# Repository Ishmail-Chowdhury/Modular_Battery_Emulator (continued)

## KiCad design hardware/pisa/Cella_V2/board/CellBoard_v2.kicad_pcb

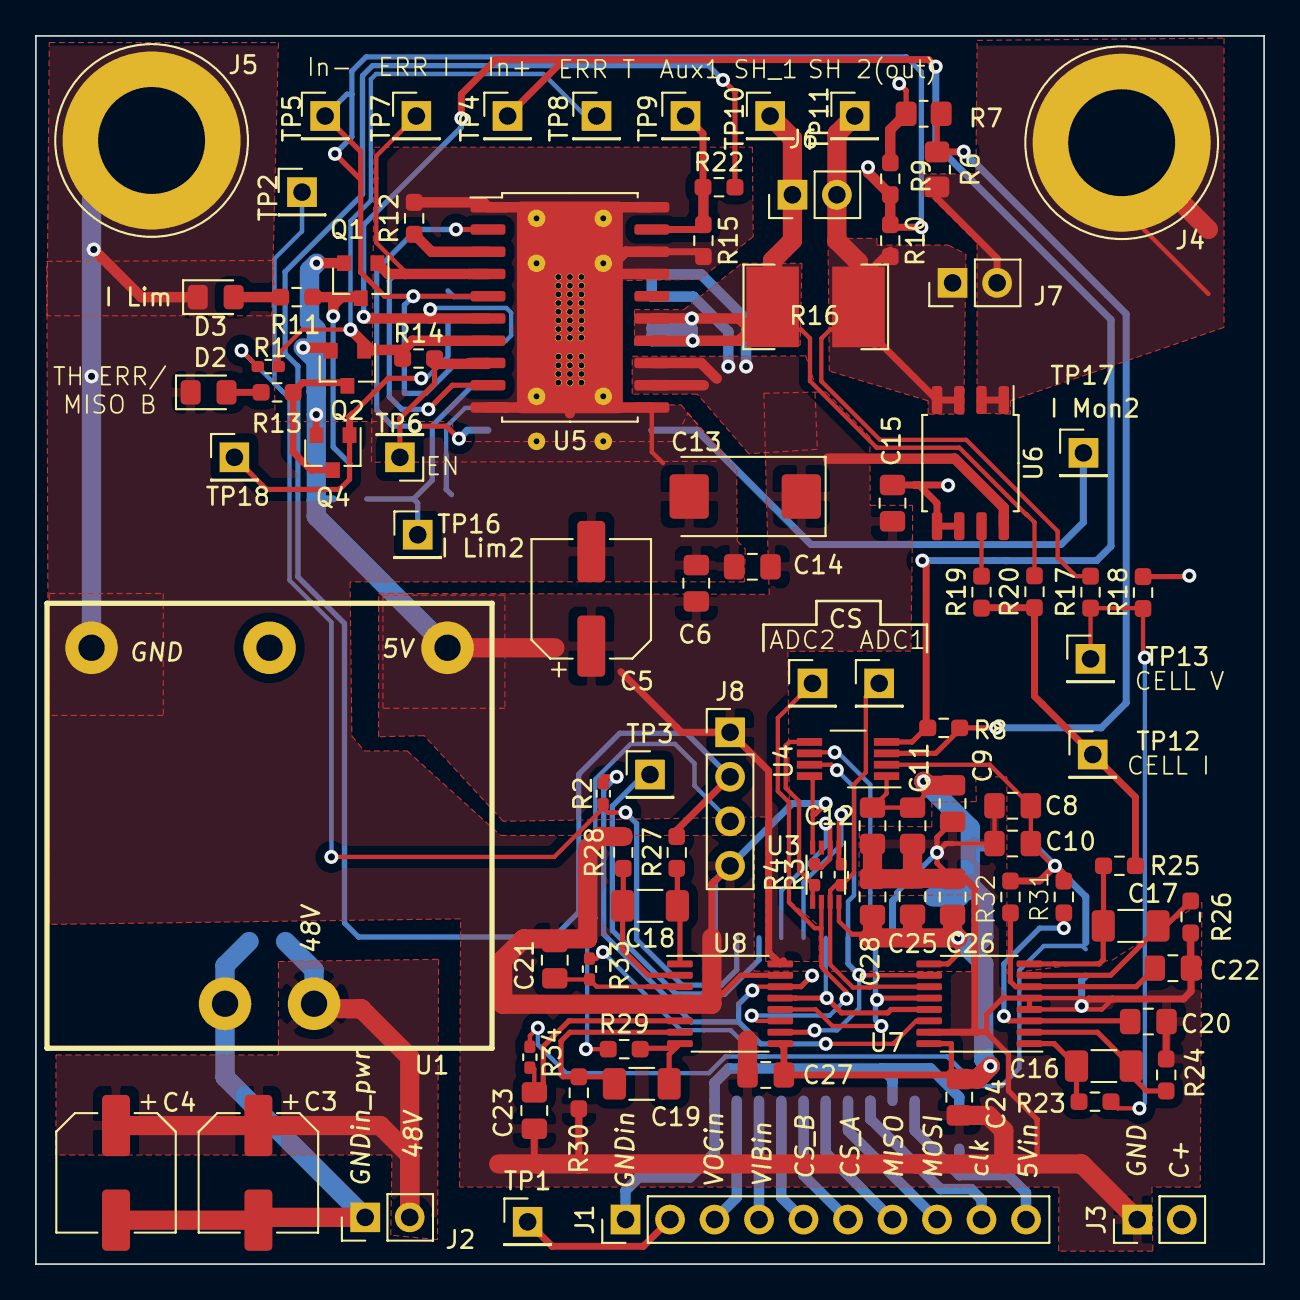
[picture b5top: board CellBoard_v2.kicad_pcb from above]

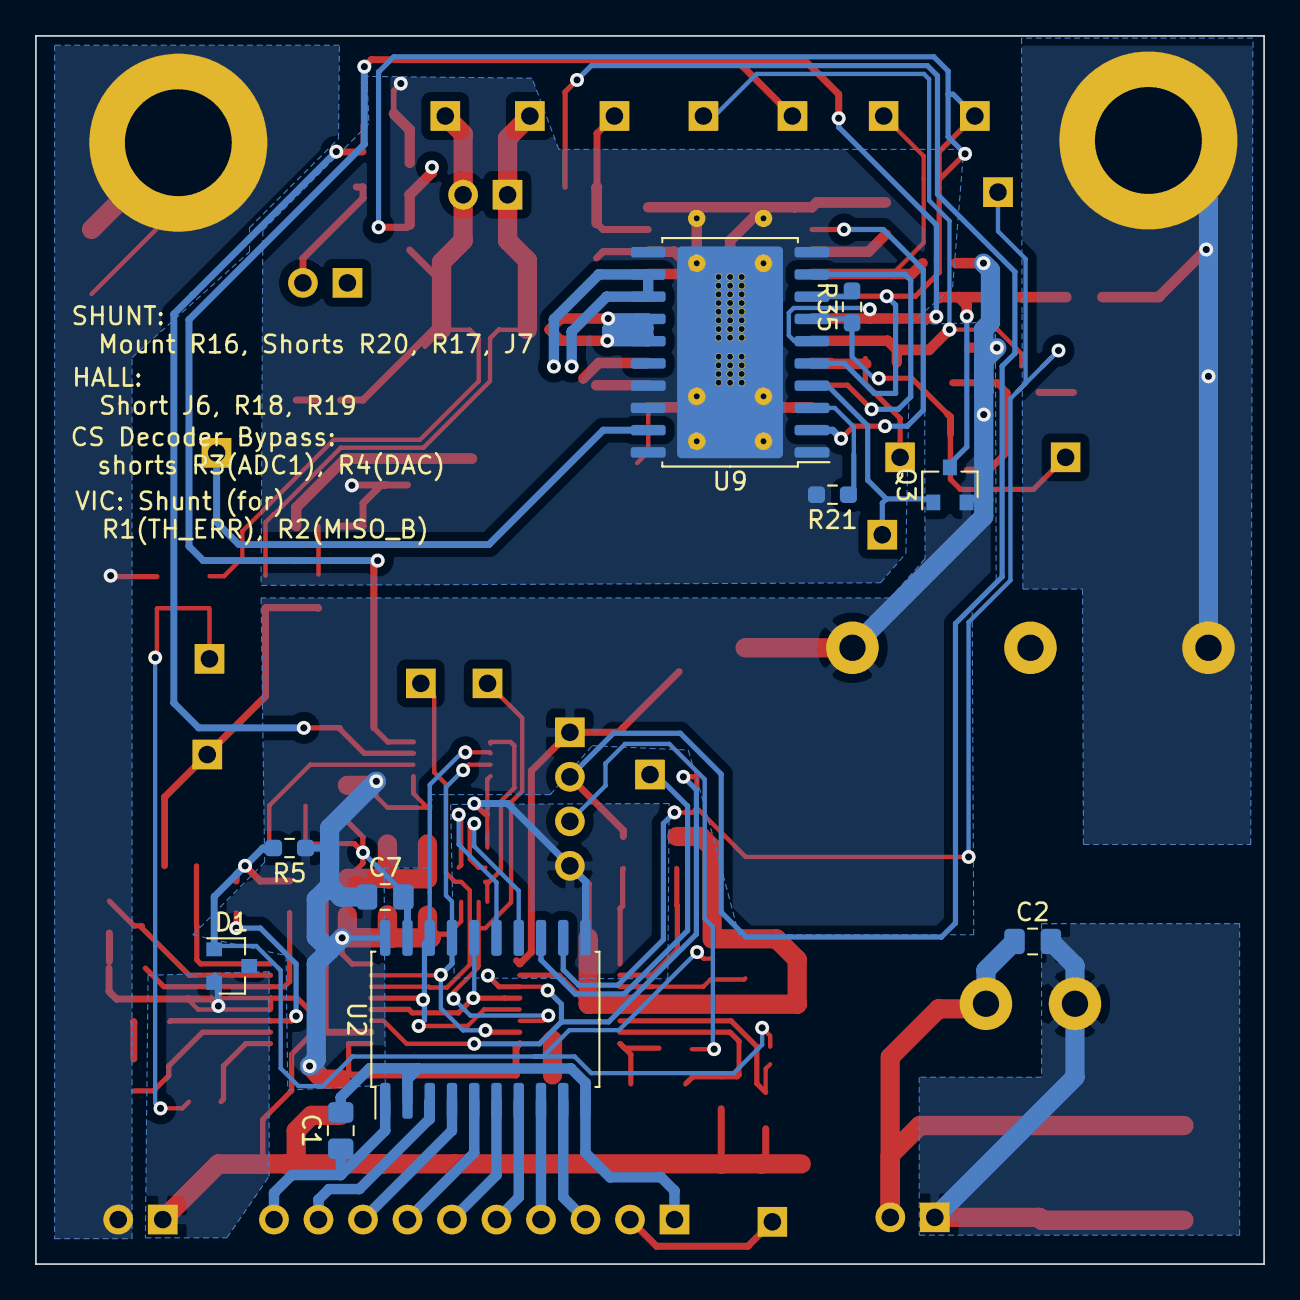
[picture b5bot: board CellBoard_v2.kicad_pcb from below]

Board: 2 copper layers, 70.1 x 70.1 mm, 105 parts (10 on the bottom side), 65 nets.

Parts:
C1, C2, C6, C7, C10, C12, C14, C15, C28: 0.1uF; C_0805_2012Metric_Pad1.18x1.45mm_HandSolder
C3, C4, C5: 10uF; CP_Elec_6.3x7.7
C8, C11: 1uF; C_0805_2012Metric_Pad1.18x1.45mm_HandSolder
C9, C20, C22, C24, C26: 10u; C_0805_2012Metric_Pad1.18x1.45mm_HandSolder
C13: 47uF; CP_EIA-7343-31_Kemet-D_Pad2.25x2.55mm_HandSolder
C16, C17: 82n; C_1206_3216Metric_Pad1.33x1.80mm_HandSolder
C18, C19: DNM; C_1206_3216Metric_Pad1.33x1.80mm_HandSolder
C21, C23, C25, C27: DNM; C_0805_2012Metric_Pad1.18x1.45mm_HandSolder
D1: 2.5 Ref; SOT-23
D2: ORANGE LED; D_0805_2012Metric_Pad1.15x1.40mm_HandSolder
D3: RED LED; D_0805_2012Metric_Pad1.15x1.40mm_HandSolder
J1: ISO COM; PinHeader_1x10_P2.54mm_Vertical
J2: Power; PinHeader_1x02_P2.54mm_Vertical
J3: C_in; PinHeader_1x02_P2.54mm_Vertical
J4: C+; Banana_Jack_1Pin
J5: C-; Banana_Jack_1Pin
J6, J7: Bypass; PinHeader_1x02_P2.54mm_Vertical
J8: AUX; PinHeader_1x04_P2.54mm_Vertical
Q1, Q2, Q3, Q4: DMP10H4D2S-7; SOT-23
R1, R2, R3, R4, R33, R34: DNM; R_0402_1005Metric_Pad0.72x0.64mm_HandSolder
R5: 2.2k; R_0603_1608Metric_Pad0.98x0.95mm_HandSolder
R6, R7: DNM; R_0805_2012Metric_Pad1.20x1.40mm_HandSolder
R8, R14, R17, R20, R35: 0; R_0603_1608Metric_Pad0.98x0.95mm_HandSolder
R9, R10, R12, R21: 10k; R_0603_1608Metric_Pad0.98x0.95mm_HandSolder
R11, R13: 620; R_0603_1608Metric_Pad0.98x0.95mm_HandSolder
R15, R18, R19, R22, R27, R28, R29, R30, R31, R32: DNM; R_0603_1608Metric_Pad0.98x0.95mm_HandSolder
R16: 70m; Shunt
R23, R24, R25, R26: 10; R_0603_1608Metric_Pad0.98x0.95mm_HandSolder
TP1, TP2, TP3, TP4, TP5, TP10, TP11, TP12, TP13, TP14: TestPoint; PinHeader_1x01_P2.54mm_Vertical
TP6: EN; PinHeader_1x01_P2.54mm_Vertical
TP7: I_LIM_FL; PinHeader_1x01_P2.54mm_Vertical
TP8: TH_FL; PinHeader_1x01_P2.54mm_Vertical
TP9: IMon; PinHeader_1x01_P2.54mm_Vertical
TP15: CS_ADC2; PinHeader_1x01_P2.54mm_Vertical
TP16: I_LIM_FL2; PinHeader_1x01_P2.54mm_Vertical
TP17: IMon2; PinHeader_1x01_P2.54mm_Vertical
TP18: TH_FL2; PinHeader_1x01_P2.54mm_Vertical
U1: URB4805YMD-10WR3; URB4805YMD-6WR3
U2: ADUM4151; SOIC-20W_7.5x12.8mm_P1.27mm
U3: 74LVC1G139; VSSOP-8_2.3x2mm_P0.5mm
U4: DAC8501; VSSOP-8_3.0x3.0mm_P0.65mm
U5: OPA569; OPA569AIDWP
U6: TMCS1101A4BQDRQ1; SOIC-8_5.275x5.275mm_P1.27mm
U7: ADS8353IPWR; TSSOP-16_4.4x5mm_P0.65mm
U8: DNM; TSSOP-16_4.4x5mm_P0.65mm
U9: OPA569; OPA569AIDWP_No_vias

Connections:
+5V: C5.1, C6.1, C7.1, C9.1, C11.1, C12.1, C13.1, C14.1, C15.1, C24.1, C25.1, C26.1, C27.1, C28.1, J8.1, Q1.2, Q2.2, Q3.2, Q4.2, R5.1, U1.3, U2.20, U3.8, U4.1, U5.12, U5.13, U6.8, U7.9, U7.16, U8.9, U8.16, U9.12, U9.13
/2.5_ref: C8.1, C10.1, D1.1, R5.2, R31.1, R32.1, R33.1, R34.1, U4.2
/5V_in: C1.1, J1.10, U2.1
/48V: C2.1, C3.1, C4.1, J2.2, U1.2
/C+: J3.2, J4.1, J7.2, R6.1, R18.2, U6.1, U6.2
/CLK: U2.18, U4.6, U7.12, U8.12
/CLK_in: J1.9, U2.3
/CS_A: J1.6, U2.6
/CS_ADC1\: R3.1, TP14.1, U3.7, U7.11
/CS_ADC2\: TP15.1, U3.6, U8.11
/CS_B: J1.5, U2.7
/CS_DAC\: R4.1, U3.5, U4.5
/GND_in_pwr: C2.2, C3.2, C4.2, J2.1, U1.1
/GND_in_sig: C1.2, J1.1, U2.2, U2.10
/MISO: U2.16, U7.13, U8.13
/MISO_B: R2.2, U7.14, U8.14
/MISO_in: J1.7, U2.5
/MOSI: U2.17, U4.7, U7.10, U8.10
/MOSI_in: J1.8, U2.4
/TH_ERROR: Q2.1, R1.2, R14.1, TP8.1, U5.7
/VIB_in: J1.4, U2.8
/VOC_in: J1.3, U2.9
/Voltage_generator/CELL_I: R19.1, R20.1, R25.1, TP12.1
/Voltage_generator/CELL_V: R17.1, R18.1, R23.1, TP13.1
/Voltage_generator/I_LIM_FL: Q1.1, TP7.1, U5.4
/Voltage_generator/I_LIM_FL2: Q3.1, TP16.1, U9.4
/Voltage_generator/TH_FL2: Q4.1, R35.1, TP18.1, U9.7
/Voltage_measurement/Aux_1: R15.1, R22.1, TP9.1, U5.19
GND: C5.2, C6.2, C7.2, C8.2, C9.2, C10.2, C11.2, C12.2, C13.2, C14.2, C15.2, C20.2, C21.2, C22.2, C23.2, C24.2, C25.2, C26.2, C27.2, C28.2, D1.2, D2.1, D3.1, J3.1, J5.1, J8.4, R7.2, R9.2, R12.2, R15.2, R21.2, R24.1, R26.1, R28.1, R30.1, U1.5, U2.11, U2.19, U3.4, U4.8, U5.1, U5.10, U5.11, U5.17, U5.18, U5.20, U5.21, U6.5, U6.6, U7.4, U7.5, U7.15, U8.4, U8.5, U8.15, U9.1, U9.10, U9.11, U9.17, U9.18, U9.20, U9.21
unnamed: C16.1, R23.2, U7.1
unnamed: C16.2, R24.2, U7.2
unnamed: C17.1, R25.2, U7.8
unnamed: C17.2, R26.2, U7.7
unnamed: C18.1, R27.2, U8.1
unnamed: C18.2, R28.2, U8.2
unnamed: C19.1, R29.2, U8.8
unnamed: C19.2, R30.2, U8.7
unnamed: C20.1, R31.2, U7.3
unnamed: C21.1, R33.2, U8.3
unnamed: C22.1, R32.2, U7.6
unnamed: C23.1, R34.2, U8.6
unnamed: D2.2, R13.2
unnamed: D3.2, R11.2
unnamed: J1.2, TP1.1
unnamed: J6.1, R16.1, R20.2, TP10.1, U5.14, U5.15, U9.14, U9.15
unnamed: J6.2, J7.1, R10.2, R16.2, R17.2, TP11.1, U6.3, U6.4
unnamed: J8.2, R22.2, R27.1
unnamed: J8.3, R29.1
unnamed: Q1.3, Q3.3, R11.1
unnamed: Q2.3, Q4.3, R13.1
unnamed: R1.1, R2.1, TP2.1, U2.12
unnamed: R3.2, U2.15, U3.1
unnamed: R4.2, U2.14, U3.2
unnamed: R6.2, R7.1, R8.2, U4.3
unnamed: R8.1, TP4.1, U4.4, U5.6, U9.6
unnamed: R9.1, R10.1, TP5.1, U5.5, U9.5
unnamed: R12.1, U5.3
unnamed: R14.2, TP6.1, U5.8
unnamed: R19.2, U6.7
unnamed: R21.1, U9.3
unnamed: R35.2, U9.8
unnamed: TP3.1, U2.13
unnamed: TP17.1, U9.19
unnamed: U5.2, U9.2
unnamed: U5.9, U9.9
